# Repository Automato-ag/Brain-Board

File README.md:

# Brain Board — Automato Ag

Firmware and documentation for the **Automato Brain Board V2.0**, an ESP32-C6 based agricultural IoT node with onboard temperature, humidity, and light sensing, ESP-NOW mesh networking, relay control, and a self-hosted web dashboard served directly from the board.

---

## Hardware

| Component | Details |
|---|---|
| MCU | ESP32-C6-MINI-1-N4, 160 MHz, 4 MB Flash |
| Temp/Humidity | SHTC3 — I2C 0x70 (fixed) |
| Light | TSL2591 — I2C 0x29 (fixed) |
| I2C Bus | SDA = IO6, SCL = IO7 |
| Blue LED | IO23 |
| Red LED | IO22 |
| Boot Button | IO9 — see Boot Button section below |
| Qwiic/STEMMA QT | J2, J3 — GND / 3V3 / SDA / SCL |
| Logic Level | 3.3V only — GPIO pins not 5V tolerant |

See [`hardware/Brain_Board_Reference.md`](hardware/Brain_Board_Reference.md) for full pinout and hardware notes.

---

## Firmware

### Current Version

| Sketch | Version |
|---|---|
| [`BrainBoard_v110`](firmware/BrainBoard/BrainBoard_v110/) | **v1.1.0** |

All boards run the same unified firmware. There is no separate Host or Remote build — role (gateway, relay, isolated) is determined automatically at runtime based on WiFi connectivity.

### Required Libraries

Install all of the following via **Arduino Library Manager**:

- `Adafruit SHTC3 Library`
- `Adafruit TSL2591`
- `Adafruit BusIO` *(installed automatically as dependency)*
- `Adafruit Unified Sensor` *(installed automatically as dependency)*
- `SparkFun TCA9534` *(for Qwiic GPIO relay control)*

### Arduino IDE Settings

| Setting | Value |
|---|---|
| Board | ESP32C6 Dev Module |
| USB CDC On Boot | **Enabled** — required; board crashes on Serial without this |
| Partition Scheme | **Custom** — required; uses `partitions.csv` in sketch folder |
| Upload Speed | 921600 |

> **Note:** USB CDC on Boot must be re-enabled each Arduino IDE session — it does not always persist.

### First Flash

1. Open `BrainBoard_v110/BrainBoard_v110.ino` in Arduino IDE
2. Set board settings as above
3. **Sketch → Upload** — flash firmware
4. **Tools → ESP32 Sketch Data Upload** — upload `data/` folder to LittleFS
5. Open Serial Monitor at 115200 baud, press RESET
6. Connect phone or laptop to the `Automato-XXXX` WiFi network
7. Open `http://192.168.4.1/setup` — enter your Network Name, password, and WiFi credentials
8. Board joins your network and is accessible at `http://networkname.local`

### OTA Updates (after first flash)

- Navigate to `http://boardname.local/update` or `http://192.168.4.1/update`
- Upload new firmware `.bin` or new LittleFS filesystem image
- Firmware and webapp update independently — UI changes do not require reflashing firmware

### Boot Button (IO9)

| Action | Behavior |
|---|---|
| Hold 5s at **startup** | Clears all stored credentials and settings, then reboots |
| Short press during **runtime** | Opens a 10-minute SoftAP access window — board stays accessible at `192.168.4.1` even when on WiFi (useful for field configuration) |

---

## Dashboard

The Brain Board serves a complete webapp directly from its own flash memory — no internet, cloud, or external server required. Works in a field with no cell service.

### Tabs

| Tab | Description | Status |
|---|---|---|
| Dashboard | Live sensor readings, relay control, Agri Data sidebar | Live |
| Devices | Local + peer I2C scan, user-defined device labels, address reference | Live |
| Rules | Automation rule engine — local and cross-board conditions | v1.2 |
| Settings | Display & Behavior (units, refresh rate, auto-sync), Agri Data Sources, Board Settings | Live |
| Network | Mesh topology — board roles, peers, gateway address | Live |

### HTTP Endpoints

| Endpoint | Method | Description |
|---|---|---|
| `/` | GET | Dashboard webapp (served from LittleFS) |
| `/data` | GET | Sensor JSON + relay state + network info |
| `/peers` | GET | Peer list JSON |
| `/version` | GET | Firmware + webapp version, mDNS name, network name |
| `/relay` | GET | Relay control (`?state=0\|1`, `?override=auto`) |
| `/relay/status` | GET | Relay state JSON |
| `/i2c-scan` | GET | Local I2C bus scan |
| `/remote-scan` | POST/GET | Peer I2C scan via ESP-NOW |
| `/time` | POST | Set board time from browser |
| `/settings` | POST | Save board name / Network Name / password |
| `/proxy` | GET | HTTPS relay — board fetches external API on browser's behalf (`?url=`); allowlisted domains only |
| `/prefs` | GET | Read dashboard preferences from LittleFS (`/prefs.json`) |
| `/prefs` | POST | Write dashboard preferences JSON to LittleFS |
| `/setup` | GET/POST | WiFi provisioning form |
| `/wifi/reset` | POST | Clear WiFi credentials + reboot |
| `/update` | GET | OTA update UI |
| `/update/firmware` | POST | Flash new firmware `.bin` |
| `/update/filesystem` | POST | Flash new LittleFS image |

### Agri Data Sidebar

External API calls are routed through the board's `/proxy` endpoint so they work when connected to the board's SoftAP (phone in the field with no direct internet). All sources are free and require no API keys.

Data sources can be enabled or disabled individually from **Settings → Agri Data Sources**.

| Parameter Group | Source |
|---|---|
| Weather, Wind, Cloud Cover, Outdoor Humidity | Open-Meteo |
| Solar, UV Index, Shortwave Radiation | Open-Meteo |
| First Light, Sunrise, Solar Noon, Sunset, Day Length | Sunrise-Sunset.org |
| Soil Temperature and Moisture, ET₀, VPD | Open-Meteo |
| Frost Risk (derived) | Open-Meteo (radiative cooling model) |
| Growing Degree Days — season to date (derived) | Open-Meteo + ERA5 archive |
| Chill Hours — season to date (derived) | Open-Meteo + ERA5 archive |
| Photoperiod — day length classification (derived) | Sunrise-Sunset.org |
| Moon Phase, Moonrise, Moonset | USNO + Sunrise-Sunset.org |
| NWS Frost Alerts | NOAA National Weather Service |
| PM2.5, Pollen | Open-Meteo Air Quality |
| DLI Accumulator (onboard sensor) | TSL2591 lux — accumulated in firmware |

---

## ESP-NOW Mesh

All Brain Boards on the same Network Name automatically form a mesh using ESP-NOW. No configuration required beyond giving boards the same Network Name in `/setup`.

| Role | Condition | Behavior |
|---|---|---|
| Gateway | Board has active WiFi | Serves dashboard at `networkname.local`; syncs NTP time; relays peer sensor data |
| Relay | No WiFi, peer discovered | Seeks mesh channel, locks on discovery, forwards sensor data to gateway via ESP-NOW |
| Isolated | No WiFi, no peers found | Seeks continuously; accessible at `192.168.4.1` via its own SoftAP |

**Channel seek:** Non-WiFi boards cycle through channels 1–11 (US), restarting their SoftAP on each channel to keep the radio active for ESP-NOW reception. Lock occurs on first matching MSG_HELLO beacon.

**Plugin hooks:** Add a `custom.ino` file to the sketch folder to extend functionality without modifying core firmware. Available hooks: `customSetup()`, `customLoop()`, `customDataJSON()`.

---

## Relay Control

- GPIO expander: SparkFun Qwiic GPIO (TCA9534) at I2C address 0x27, connected via Qwiic cable
- Relay defaults **OFF** at all times — boot, sensor failure, I2C error, connectivity loss
- Manual ON/OFF toggle in dashboard always overrides automation
- Rule engine arriving in v1.2

## Relay Safety Contract

Relays default **OFF** under all failure conditions: boot, sensor failure, WiFi loss, cloud loss, browser closed, no rules configured, conflicting rules, hardware expander not found.

**There is no condition under which a relay defaults ON.**

---

## Roadmap

| Version | Feature | Status |
|---|---|---|
| v0.8.1 | Tab navigation shell, I2C Scanner tab, `/i2c-scan` endpoint | Complete |
| v0.9 | Devices tab, remote I2C scan via ESP-NOW, Network Name in `/setup` | Complete |
| v1.0 | Settings tab, Network tab stub, `POST /settings` endpoint | Complete |
| v1.1 | ESP-NOW mesh — unified firmware, MSG_HELLO beacon, dynamic gateway, `networkname.local`, 1-hop relay, live Network tab, plugin hooks | Complete |
| v1.2 | Rules tab — firmware rule engine, LittleFS persistence, local + peer conditions, recipe database | Next |
| v1.3 | Multi-hop relay, routing tables, cross-board rules | Planned |

---

## Repository Structure

```
Brain-Board/
├── README.md
├── CHANGELOG.md
├── LICENSE
├── .gitignore
├── firmware/
│   ├── BrainBoard/
│   │   └── BrainBoard_v110/            <- current (v1.1)
│   │       ├── BrainBoard_v110.ino
│   │       ├── partitions.csv
│   │       └── data/
│   │           ├── index.html
│   │           └── version.txt
│   ├── BrainBoard_Host/                <- legacy (pre-v1.1)
│   └── BrainBoard_Remote/              <- legacy (pre-v1.1, retired)
├── docs/
│   ├── Roadmap.md
│   ├── QuickStart.md
│   ├── RelayControl.md
│   ├── AgriDataSidebar.md
│   ├── ESP32C6_Capabilities.md
│   ├── I2C_Address_Map.md
│   └── ProductFamily.md
├── hardware/
│   ├── README.md
│   ├── Brain_Board_Reference.md
│   └── kicad/
│       └── Brain_Board_V2.0/
└── tools/
    └── I2C_Scanner/
        └── I2C_Scanner.ino
```

---

## License

MIT License — see [LICENSE](LICENSE) for details.

---

*Automato Ag — [automato.ag](https://automato.ag)*

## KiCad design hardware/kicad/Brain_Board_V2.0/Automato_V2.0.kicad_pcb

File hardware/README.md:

# Automato Brain Board V2.0 — Hardware Files

This folder contains hardware design files for the Automato Brain Board V2.0.

---

## Files

### Brain_Board_Reference.md
Complete hardware reference — MCU specs, pin definitions, I2C addresses, power rails, and peripheral wiring.

### kicad/Brain_Board_V2.0/
KiCad 9.0 design files for the Brain Board V2.0 PCB.

| File | Description |
|---|---|
| `Automato_V2.0.kicad_sch` | Schematic |
| `Automato_V2.0.kicad_pcb` | PCB layout |
| `Automato_V2.0.kicad_pro` | KiCad project file |

**To open:** Install [KiCad 9.0](https://www.kicad.org/download/) and open `Automato_V2.0.kicad_pro`.

---

## Key Specs

| Property | Value |
|---|---|
| MCU | ESP32-C6-MINI-1-N4 |
| Flash | 4 MB |
| Onboard sensors | SHTC3 (temp/humidity, 0x70), TSL2591 (light, 0x29) |
| I2C | SDA = IO6, SCL = IO7 |
| Connector | 2× Qwiic (JST-PH 4-pin, 3.3V) |
| Power | USB-C, 3.3V logic |
| Logic level | 3.3V — GPIO pins not 5V tolerant |

---

## Onboard I2C Addresses (fixed — cannot be changed)

| Address | Device | Function |
|---|---|---|
| 0x29 | TSL2591 | Ambient light |
| 0x70 | SHTC3 | Temperature + humidity |

### Reserved addresses (next revision)
| Address | Device | Notes |
|---|---|---|
| 0x68 | DS3231 RTC | Onboard RTC planned for next Brain Board revision |

---

## Architecture Note

The Brain Board is always a discrete, standalone PCB. It is never integrated into a peripheral board. All output capability (relay, MOSFET, GPIO expansion) lives on separate peripheral boards connected via cable.

See [`docs/Roadmap.md`](../docs/Roadmap.md) for full hardware roadmap including the 6-pin Automato connector specification and planned peripheral board lineup.

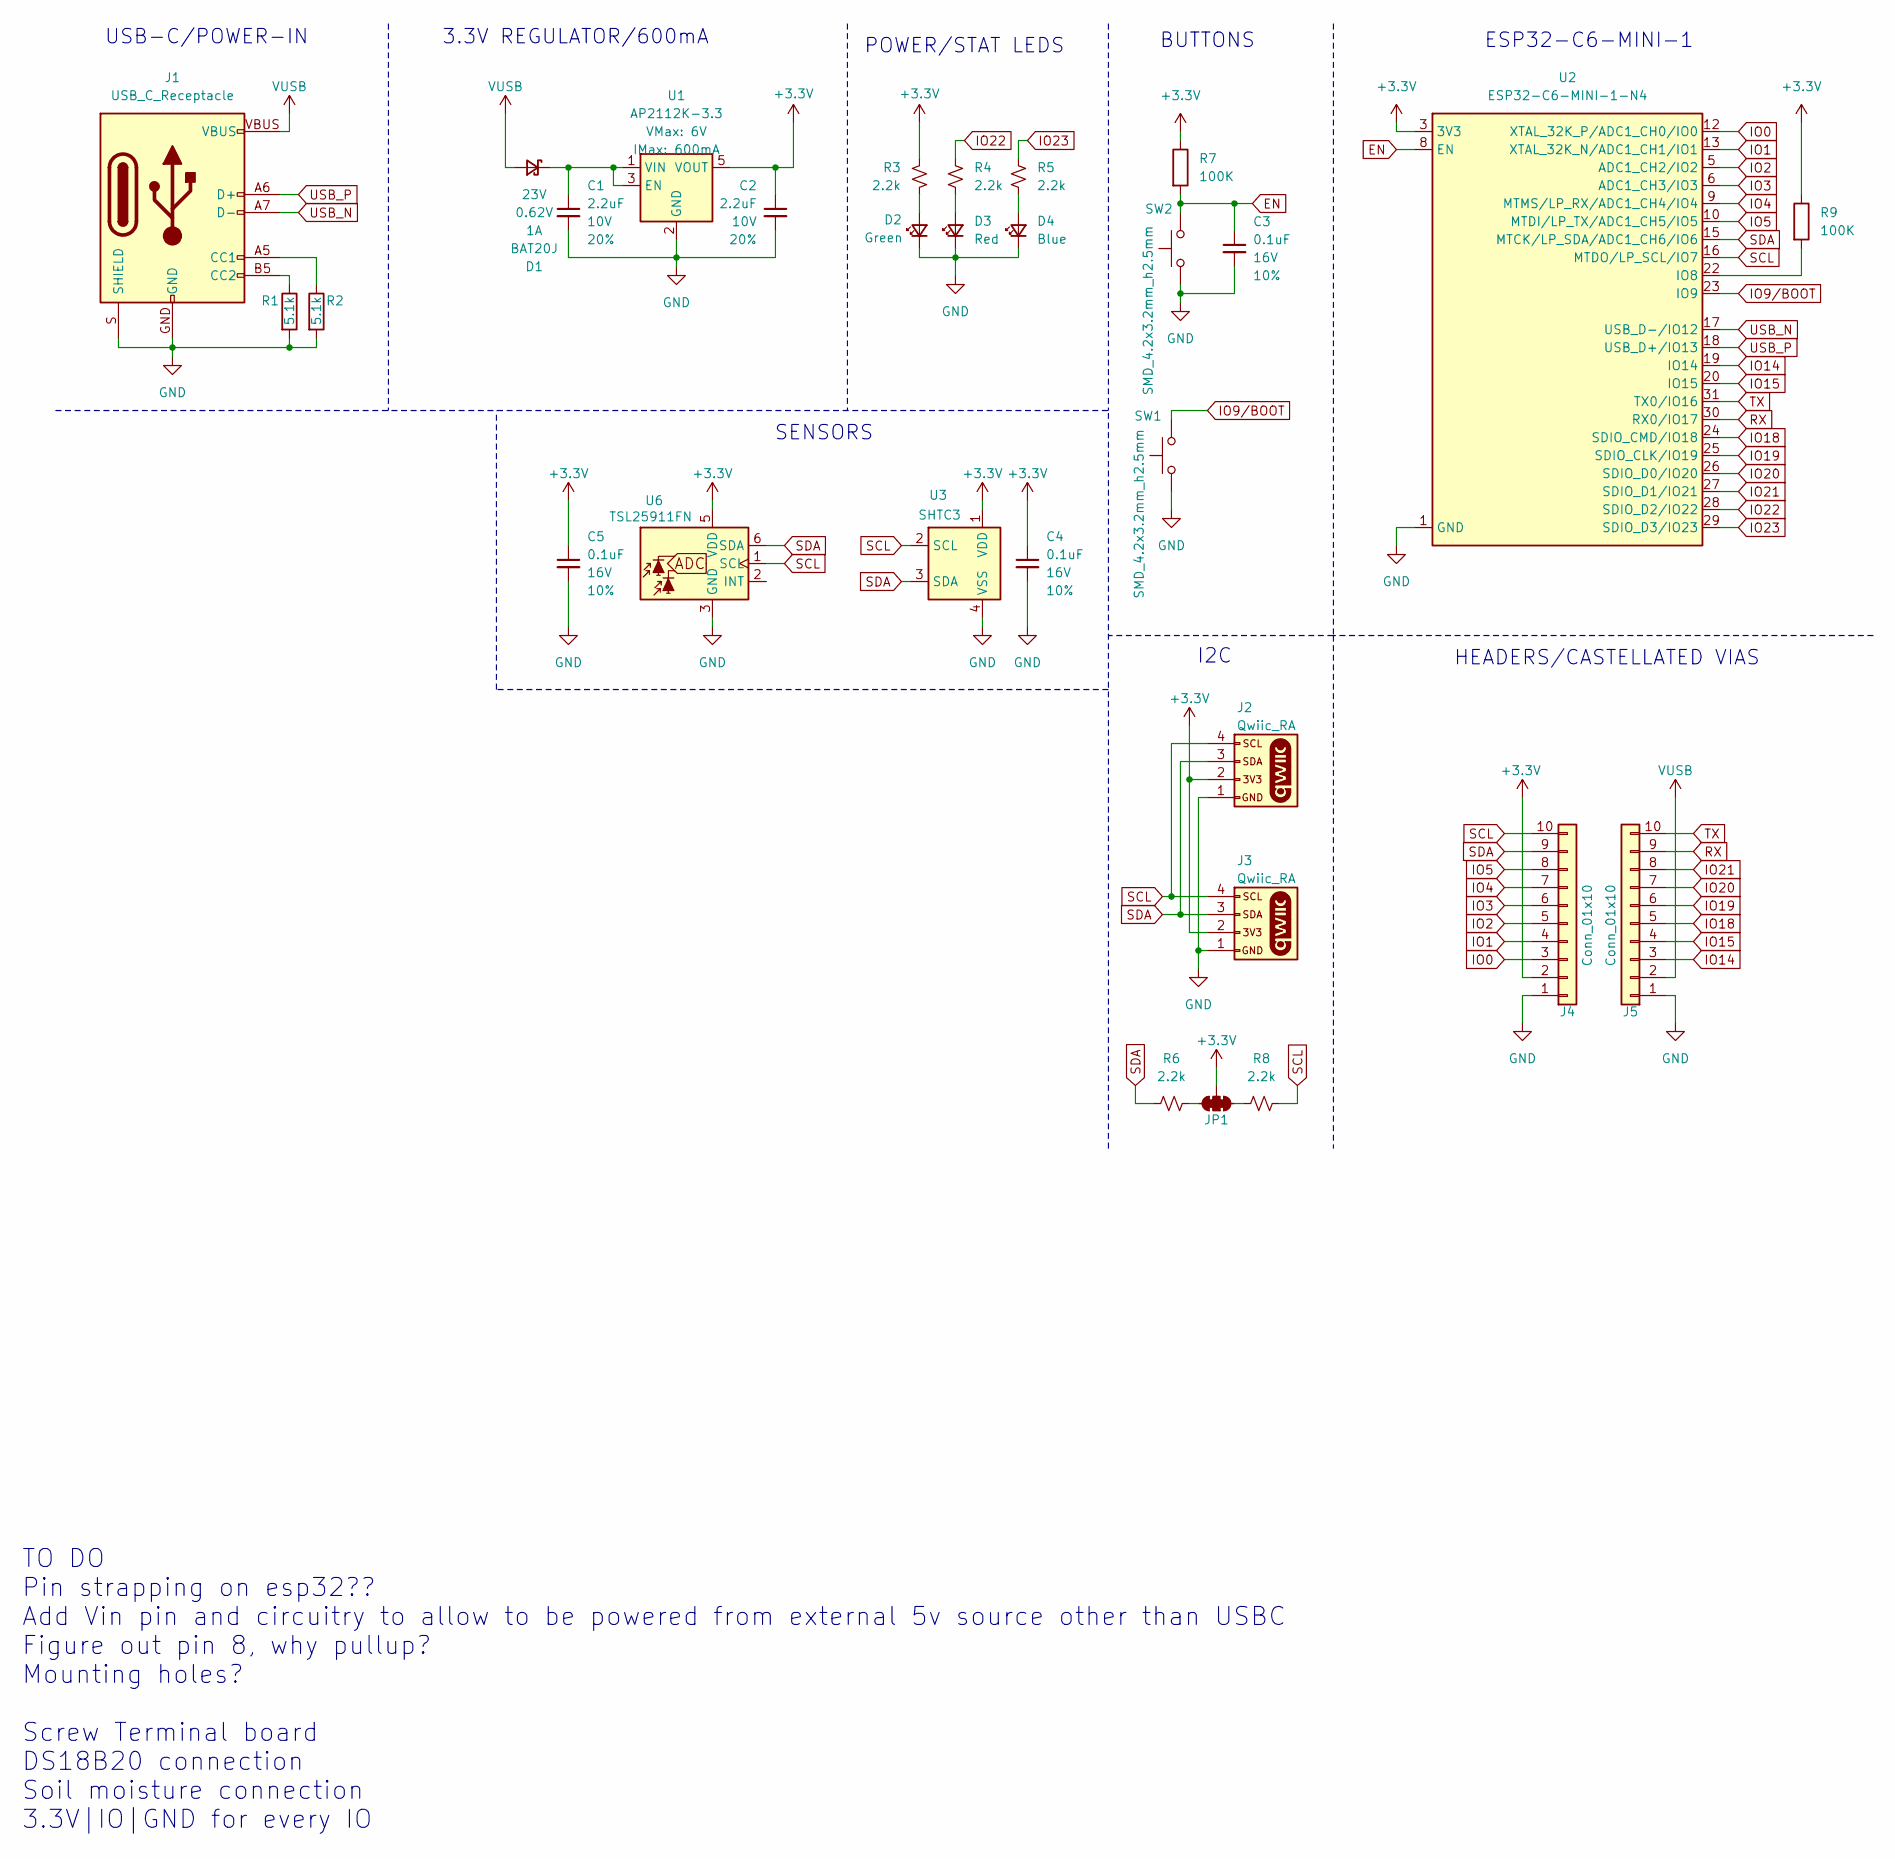
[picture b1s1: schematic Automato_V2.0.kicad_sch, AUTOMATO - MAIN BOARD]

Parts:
C1, C2: 2.2uF; C_0603_1608Metric; Voltage 10V; Tolerance 20%
C3, C4, C5: 0.1uF; C_0402_1005Metric; Voltage 16V; Tolerance 10%
D1: BAT20J; SOD-323
D2: Green; LED_0603_1608Metric_Green
D3: Red; LED_0603_1608Metric_Red
D4: Blue; LED_0603_1608Metric_Blue
J1: USB_C_Receptacle; USB-C_16
J2, J3: Qwiic_RA; JST_SMD_1.0mm-4_Black
J4, J5: Conn_01x10; 1x10_Castellated
JP1: Jumper_3_NC-2_Trace
R1, R2: 5.1k; R_0402_1005Metric
R3, R4, R5, R6, R8: 2.2k; R_0402_1005Metric
R7, R9: 100K; R_0402_1005Metric
SW1, SW2: SMD_4.2x3.2mm_h2.5mm; Push_SMD_4.2x3.2mm
U1: AP2112K-3.3; SOT23-5
U2: ESP32-C6-MINI-1-N4; ESP32-C6-MINI-1
U3: SHTC3; Sensirion_DFN-4-1EP_2x2mm_P1mm_EP0.7x1.6mm
U6: TSL25911FN; AMS_TSL25911FN

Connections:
+3.3V: C2.1, C4.1, C5.1, J2.2, J3.2, J4.2, JP1.2 (B), R3.2, R7.1, R9.1, U1.5 (VOUT), U2.3 (3V3), U3.1 (VDD), U6.5 (VDD)
EN: C3.1, R7.2, SW2.2, U2.8 (EN)
GND: C1.2, C2.2, C3.2, C4.2, C5.2, D2.1 (K), D3.1 (K), D4.1 (K), J1.GND, J1.S (SHIELD), J2.1, J3.1, J4.1, J5.1, R1.2, R2.2, SW1.1, SW2.1, U1.2 (GND), U2.1 (GND), U2.2 (GND), U2.11 (GND), U2.14 (GND), U2.36 (GND), U2.37 (GND), U2.38 (GND), U2.39 (GND), U2.40 (GND), U2.41 (GND), U2.42 (GND), U2.43 (GND), U2.44 (GND), U2.45 (GND), U2.46 (GND), U2.47 (GND), U2.48 (GND), U2.49 (GND), U2.50 (GND), U2.51 (GND), U2.52 (GND), U2.53 (GND), U3.4 (VSS), U6.3 (GND)
IO0: J4.3, U2.12 (XTAL_32K_P/ADC1_CH0/IO0)
IO1: J4.4, U2.13 (XTAL_32K_N/ADC1_CH1/IO1)
IO2: J4.5, U2.5 (ADC1_CH2/IO2)
IO3: J4.6, U2.6 (ADC1_CH3/IO3)
IO4: J4.7, U2.9 (MTMS/LP_RX/ADC1_CH4/IO4)
IO5: J4.8, U2.10 (MTDI/LP_TX/ADC1_CH5/IO5)
IO9/BOOT: SW1.2, U2.23 (IO9)
IO14: J5.3, U2.19 (IO14)
IO15: J5.4, U2.20 (IO15)
IO18: J5.5, U2.24 (SDIO_CMD/IO18)
IO19: J5.6, U2.25 (SDIO_CLK/IO19)
IO20: J5.7, U2.26 (SDIO_D0/IO20)
IO21: J5.8, U2.27 (SDIO_D1/IO21)
IO22: R4.2, U2.28 (SDIO_D2/IO22)
IO23: R5.2, U2.29 (SDIO_D3/IO23)
unnamed: C1.1, D1.1 (K), U1.1 (VIN), U1.3 (EN)
unnamed: D2.2 (A), R3.1
unnamed: D3.2 (A), R4.1
unnamed: D4.2 (A), R5.1
unnamed: J1.A5 (CC1), R2.1
unnamed: J1.B5 (CC2), R1.1
unnamed: JP1.1 (A), R8.1
unnamed: JP1.3 (C), R6.2
unnamed: R9.2, U2.22 (IO8)
RX: J5.9, U2.30 (RX0/IO17)
SCL: J2.4, J3.4, J4.10, R8.2, U2.16 (MTDO/LP_SCL/IO7), U3.2 (SCL), U6.1 (SCL)
SDA: J2.3, J3.3, J4.9, R6.1, U2.15 (MTCK/LP_SDA/ADC1_CH6/IO6), U3.3 (SDA), U6.6 (SDA)
TX: J5.10, U2.31 (TX0/IO16)
USB_N: J1.A7 (D-), J1.B7 (D-), U2.17 (USB_D-/IO12)
USB_P: J1.A6 (D+), J1.B6 (D+), U2.18 (USB_D+/IO13)
VUSB: D1.2 (A), J1.VBUS, J5.2

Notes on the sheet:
USB-C/POWER-IN
TO DO Pin strapping on esp32?? Add Vin pin and circuitry to allow to be powered from external 5v source other than USBC Figure out pin 8, why pullup? Mounting holes? Screw Terminal board DS18B20 connection Soil moisture connection 3.3V|IO|GND for every IO
ESP32-C6-MINI-1
BUTTONS
SENSORS
POWER/STAT LEDS
I2C
HEADERS/CASTELLATED VIAS
3.3V REGULATOR/600mA

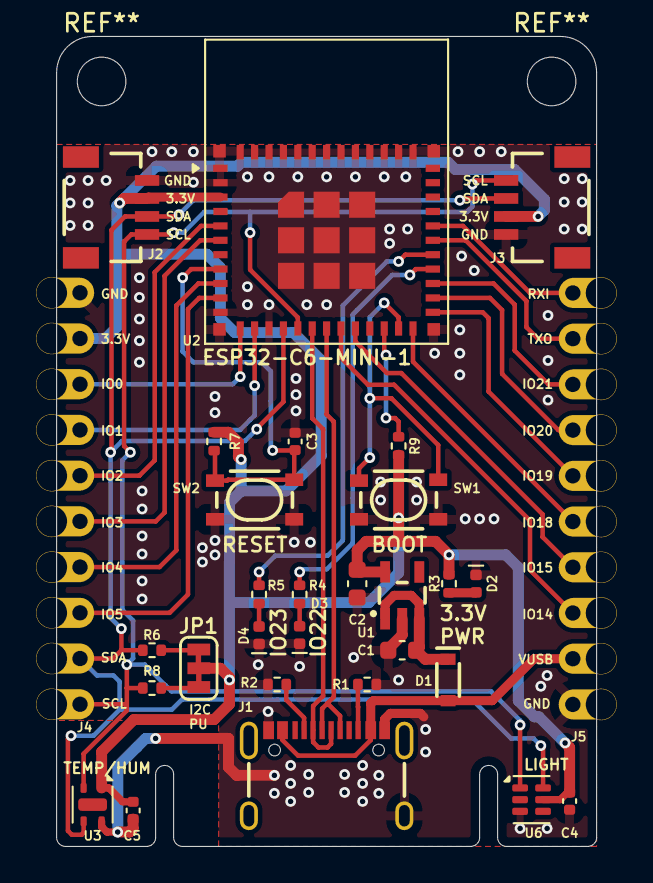
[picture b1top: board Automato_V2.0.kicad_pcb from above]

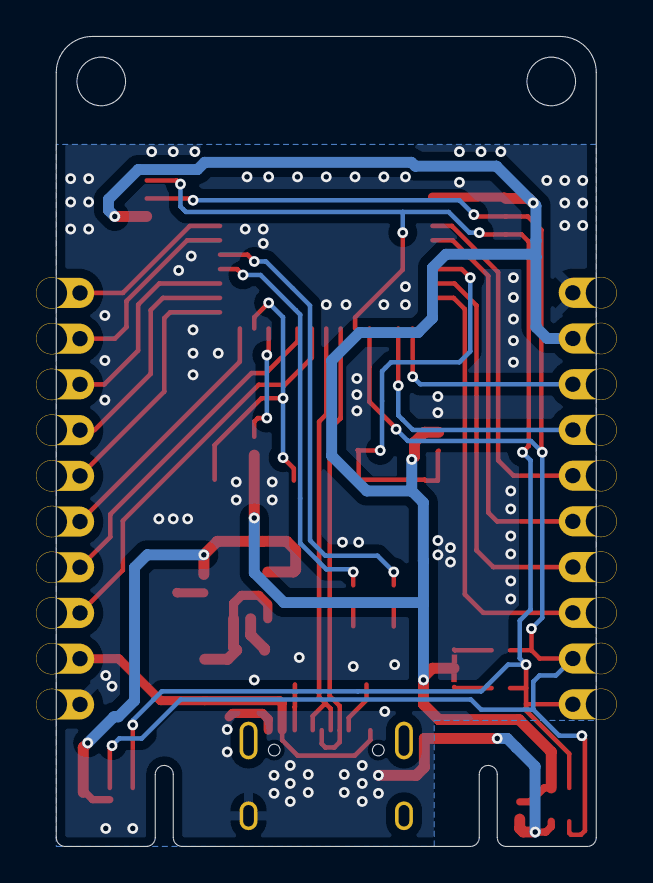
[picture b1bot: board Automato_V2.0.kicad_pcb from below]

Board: 2 copper layers, 30.0 x 45.0 mm, 30 parts (2 on the bottom side), 34 nets.

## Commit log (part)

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2026-03-12 Initial commit — Host v0.6, Remote v0.4
2026-03-12 Create ESP32C6_Capabilities.md
    Add ESP32-C6 unexplored capabilities notes
2026-03-12 Update README.md
    Add ESP32-C6 capabilities link to roadmap
2026-03-17 Sync: Roadmap, v0.6.1 address fix, I2C scanner, ESP32-C6 capabilities update
2026-03-17 Add ProductFamily.md and I2C_Address_Map.md — product architecture, connector standard, BOM analysis
2026-03-19 firmware: add BrainBoard_Host_v07 and BrainBoard_Remote_v04
2026-03-19 v0.8.0 — WiFi provisioning, mDNS, channel scan
2026-03-20 v0.8.1 — I2C Scanner tab, tab nav shell, /i2c-scan endpoint
2026-03-21 Add KiCad hardware files for Brain Board V2.0
2026-03-21 v0.8.1 — MCU Temp card, collapsible cards, hover tooltips
2026-03-22 Update roadmap: custom ESP-NOW mesh architecture, board mobility, v1.0-v1.2 scope
    - Replace ESP-Mesh-Lite with custom ESP-NOW mesh (no external dependencies)
    - Document board mobility as first-class design constraint
    - v1.1: MSG_HELLO beacon, dynamic gateway, networkname.local, 1-hop relay
    - v1.2: multi-hop relay, TTL + duplicate-drop, routing tables, unified firmware
    - v0.9 marked complete; version table updated
    - 5-tab structure documented (Network tab added as stub in v1.0)
2026-03-23 v1.0: Settings tab (functional) + Network tab (stub)
    Firmware:
    - Add POST /settings endpoint — saves board name, Network Name, and
    password to NVS without requiring WiFi credentials (POST /setup
    requires ssid field; /settings does not)
    Webapp:
    - Settings tab: pre-fills board name and network name from /version;
2026-03-23 Revise version numbering: v1.0 complete, ESP-NOW mesh moves to v1.1, Rules to v1.2, multi-hop to v1.3
2026-03-28 v1.1: ESP-NOW mesh — unified firmware, channel seek, 1-hop relay, live Network tab
    - Unified firmware: BrainBoard_Host/Remote merged into single BrainBoard build; all boards are full peers
    - MSG_HELLO beacon: auto-discovery by Network Name; boards register ESP-NOW peers without manual config
    - Dynamic gateway election: WiFi-connected board self-elects gateway; non-WiFi boards enter relay role
    - networkname.local mDNS: gateway advertises mDNS hostname derived from Network Name
    - Non-blocking channel seek: non-WiFi boards cycle channels 1–11 (US cc=01) by restarting SoftAP on each channel to keep radio active for ESP-NOW RX; locks on first HELLO match
    - 5-min seek kick: re-triggers fast be
2026-03-28 README: full rewrite for v1.1 — unified firmware, mesh, current endpoints and roadmap
2026-03-28 webapp: Settings tab redesign, PRG fix for /setup, board name labels, channel seek fix
    - Settings tab: Display & Behavior section (units, refresh rate, auto-sync time),
    Agri Data Sources submenu (source-level list + per-source parameter drill-down),
    Board Settings master-detail layout (scrollable board list + inline detail panel)
    - Peer board panel: READ ONLY badge, Boot button instruction in SoftAP access note
    - Units toggle moved from Dashboard sidebar to Settings only
    - Dashboard board columns now show actual board names from /version and /peers
